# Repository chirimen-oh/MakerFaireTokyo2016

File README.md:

# MakerFaireTokyo2016
Maker Faire Tokyo 2016のKDDI、HAKUTO、CHIRIMEN共同出展スペースにおいて展示した作品群のソースコードです。

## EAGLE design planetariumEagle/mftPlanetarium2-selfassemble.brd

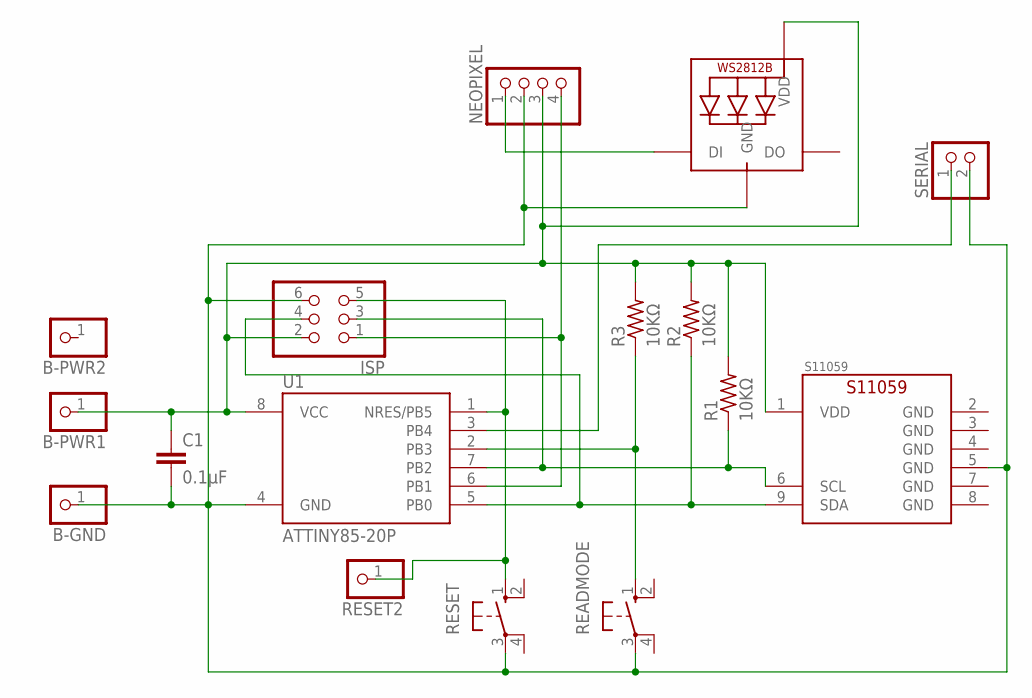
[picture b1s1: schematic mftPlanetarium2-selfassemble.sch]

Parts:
B-GND: PINHD-1X1; 1X01
B-PWR1, B-PWR2: PINHD-1X1; 1X01
C1: 0.1μF; C025-025X050
ISP: PINHD-2X3; 2X03
LED1: WS2812B5050; WS2812B
NEOPIXEL: PINHD-1X4; 1X04
R1, R2, R3: 10KΩ; 0204/7
READMODE: 10-XX; B3F-10XX
RESET: 10-XX; B3F-10XX
RESET2: PINHD-1X1; 1X01
S11059: S11059; HAMAMATSU-S11059
SERIAL: PINHD-1X2; 1X02
U1: ATTINY85-20P; PDIP08_300MIL

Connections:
GND: B-GND.1, C1.2, ISP.6, LED1.3-GND (GND), NEOPIXEL.2, READMODE.3, RESET.3, S11059.5 (GND), SERIAL.2, U1.4 (GND)
unnamed: LED1.4-DIN (DI), NEOPIXEL.1
unnamed: ISP.1, NEOPIXEL.4, U1.6 (PB1)
unnamed: SERIAL.1, U1.3 (PB4)
unnamed: ISP.5, RESET.1 (S), RESET2.1, U1.1 (NRES/PB5)
unnamed: R3.1, READMODE.1 (S), U1.2 (PB3)
PWR: B-PWR1.1, C1.1, ISP.2, LED1.1-VDD (VDD), NEOPIXEL.3, R1.2, R2.2, R3.2, S11059.1 (VDD), U1.8 (VCC)
SCL: ISP.3, R1.1, S11059.6 (SCL), U1.7 (PB2)
SDA: ISP.4, R2.1, S11059.9 (SDA), U1.5 (PB0)

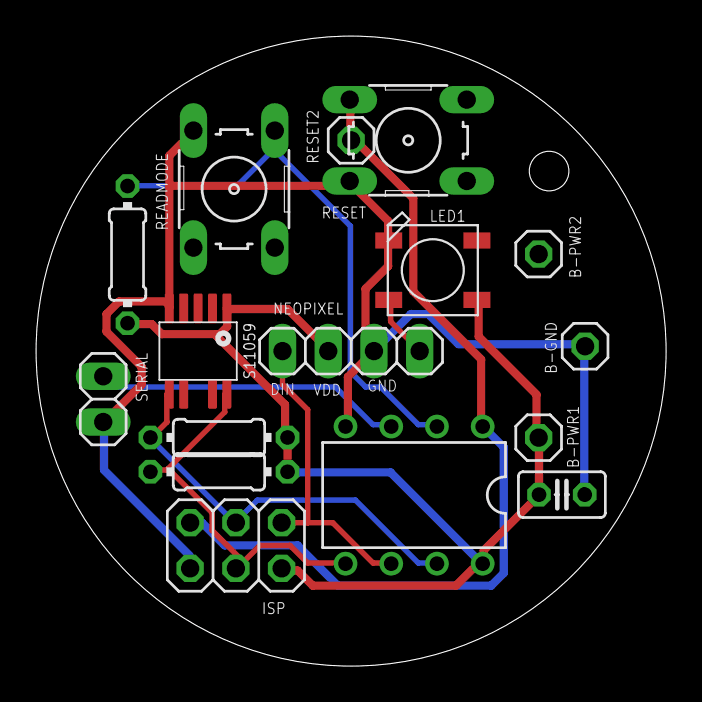
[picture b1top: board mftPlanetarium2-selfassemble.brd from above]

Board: 2 copper layers, 35.0 x 35.0 mm, 16 parts (0 on the bottom side), 9 nets.

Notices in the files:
parts and their libraries:
FaBo-Sensor: Released under the Creative Commons Attribution-ShareAlike 4.0 License
https://creativecommons.org/licenses/by-sa/4.0
